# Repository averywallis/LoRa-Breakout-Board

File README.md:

# LoRa Breakout Board
 KiCad files for an RFM95 LoRa Breakout Board

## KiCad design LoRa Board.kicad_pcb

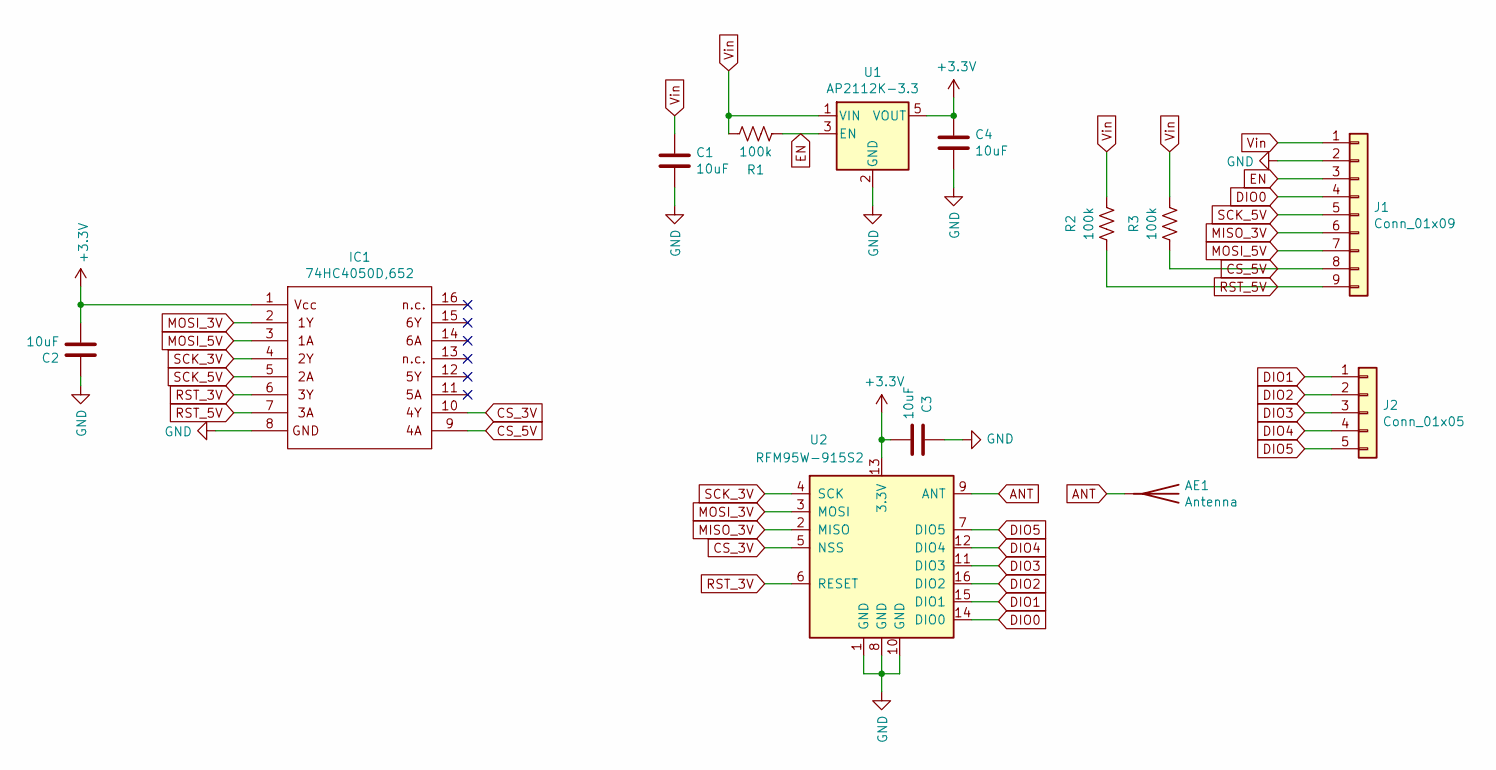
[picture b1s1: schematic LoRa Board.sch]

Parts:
AE1: Antenna; Pin_D1.0mm_L10.0mm
C1, C2, C3, C4: 10uF; C_0805_2012Metric_Pad1.15x1.40mm_HandSolder; MPN CL21A106KOQNNNG
IC1: 74HC4050D,652; SOIC127P600X175-16N; MPN 74HC4050D,652
J1: Conn_01x09; PinSocket_1x09_P2.54mm_Vertical; MPN 69190-410HLF
J2: Conn_01x05; PinSocket_1x05_P2.54mm_Vertical; MPN 69190-410HLF
R1, R2, R3: 100k; R_0805_2012Metric_Pad1.15x1.40mm_HandSolder; MPN RMCF0805JT100K
U1: AP2112K-3.3; SOT-23-5; MPN AP2112K-3.3TRG1
U2: RFM95W-915S2; HOPERF_RFM9XW_SMD; MPN RFM95W-915S2

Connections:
+3V3: C2.2, C3.2, C4.1, IC1.1, U1.5 (VOUT), U2.13 (3.3V)
ANT: AE1.1, U2.9 (ANT)
CS_3V: IC1.10, U2.5 (NSS)
CS_5V: IC1.9, J1.8, R3.1
DIO0: J1.4, U2.14 (DIO0)
DIO1: J2.1, U2.15 (DIO1)
DIO2: J2.2, U2.16 (DIO2)
DIO3: J2.3, U2.11 (DIO3)
DIO4: J2.4, U2.12 (DIO4)
DIO5: J2.5, U2.7 (DIO5)
EN: J1.3, R1.1, U1.3 (EN)
GND: C1.2, C2.1, C3.1, C4.2, IC1.8, J1.2, U1.2 (GND), U2.1 (GND), U2.8 (GND), U2.10 (GND)
MISO_3V: J1.6, U2.2 (MISO)
MOSI_3V: IC1.2, U2.3 (MOSI)
MOSI_5V: IC1.3, J1.7
RST_3V: IC1.6, U2.6 (RESET)
RST_5V: IC1.7, J1.9, R2.2
SCK_3V: IC1.4, U2.4 (SCK)
SCK_5V: IC1.5, J1.5
Vin: C1.1, J1.1, R1.2, R2.1, R3.2, U1.1 (VIN)

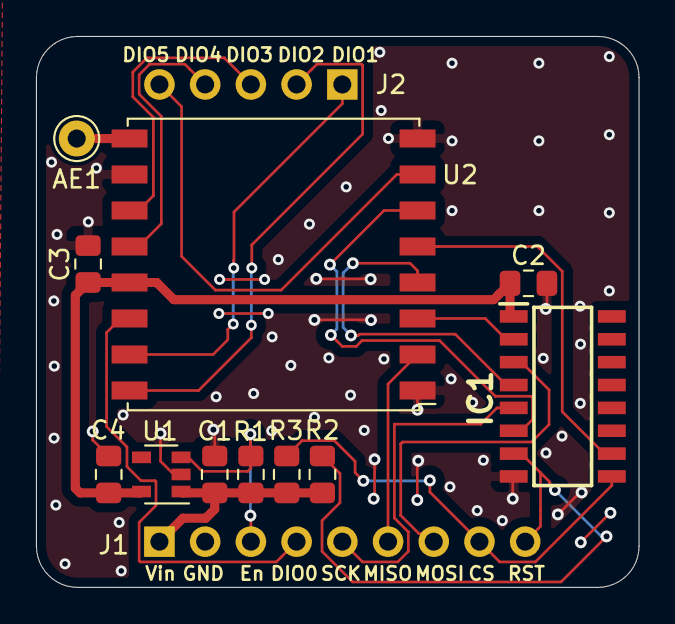
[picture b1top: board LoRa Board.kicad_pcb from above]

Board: 2 copper layers, 33.5 x 30.6 mm, 13 parts (0 on the bottom side), 20 nets.

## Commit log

2020-01-06 Reorganizing Github
2022-01-29 Create LICENSE
